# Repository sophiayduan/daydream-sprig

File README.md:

# Daydream-Sprig

#### The Daydream-Sprig is a version of the [Sprig](https://github.com/hackclub/sprig) using the bare RP2040 chip and in a vertical handheld formfactor.

I'll be setting it up the same as the Sprig. flashing Spade OS (Sprigs custom operating system)

### Features 
- All pre-exsiting sprig stuff (Rp2040, ST7735 1.8" Display, powered via 2xaaa, etc)
- 6x6mm push buttons
- Vertical handheld form factor
- 4 additional GPIOS
- Cool silkscreen art made by Erin + some stolen from the og sprig

(unlike the original sprig, this board doesn't include a speaker due to its cost)

This project was made as a lanyard for [Daydream Ottawa](https://daydream.hackclub.com/ottawa) organizers (to display their names and other cool stuff) but, I didn't end up finishing it in time oops.

## Acknowledgements
*the sprig.*

Thanks JLCPCB for sponsoring DD Ottawa and hence this project.

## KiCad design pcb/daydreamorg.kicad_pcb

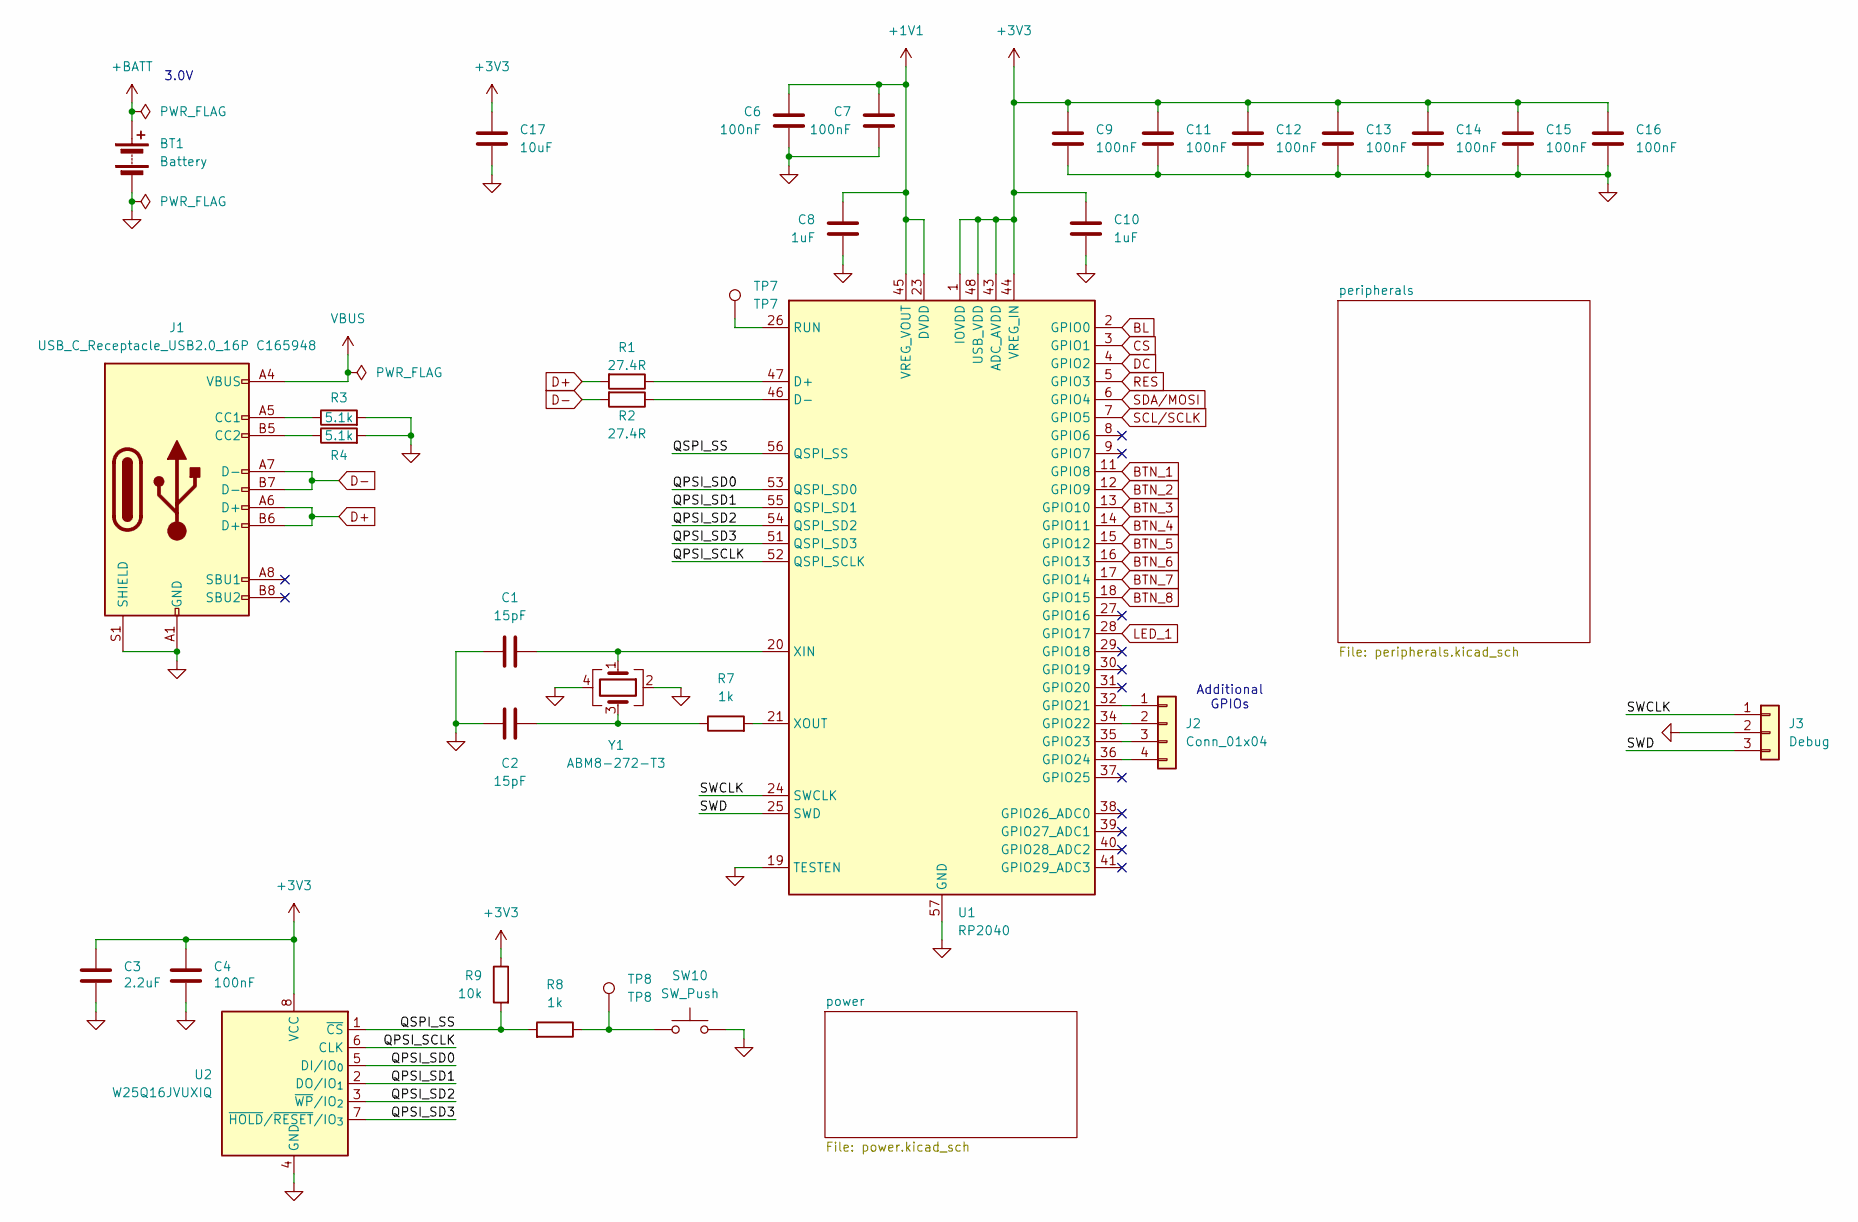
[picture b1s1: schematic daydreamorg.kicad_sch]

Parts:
BT1: Battery; BatteryHolder_Keystone_2468_2xAAA; LCSC C254917
C1, C2: 15pF; C_0402_1005Metric; LCSC C1548
C3: 2.2uF; C_0402_1005Metric; LCSC C541409
C4: 100nF; C_0603_1608Metric; LCSC C1525
C6, C7, C9, C11, C12, C13, C14, C15, C16: 100nF; C_0402_1005Metric; LCSC C1525
C8, C10: 1uF; C_0402_1005Metric; LCSC C52923
C17: 10uF; C_0805_2012Metric
J1: USB_C_Receptacle_USB2.0_16P C165948; USB_C_Receptacle_HRO_TYPE-C-31-M-12; LCSC C165948
J2: Conn_01x04; PinHeader_1x04_P2.54mm_Vertical
J3: Debug; PinHeader_1x03_P2.54mm_Vertical
R1, R2: 27.4R; R_0402_1005Metric; LCSC C25100
R3, R4: 5.1k; R_0603_1608Metric; LCSC C23186
R7, R8: 1k; R_0402_1005Metric; LCSC C11702
R9: 10k; R_0402_1005Metric
SW10: SW_Push; SW_TS-1088-AR02016; LCSC C720477
TP7: TP7; TestPoint_Pad_D2.0mm
TP8: TP8; TestPoint_Pad_D2.0mm
U1: RP2040; QFN-56-1EP_7x7mm_P0.4mm_EP3.2x3.2mm; LCSC C2040
U2: W25Q16JVUXIQ; SOIC-8_5.3x5.3mm_P1.27mm; LCSC C2843335
Y1: ABM8-272-T3; Crystal_SMD_3225-4Pin_3.2x2.5mm; LCSC C20625731

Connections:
+1V1: C6.1, C7.1, C8.1, U1.23 (DVDD), U1.45 (VREG_VOUT), U1.50 (DVDD)
+3V3: C3.1, C4.1, C9.1, C10.1, C11.1, C12.1, C13.1, C14.1, C15.1, C16.1, C17.1, R9.1, U1.1 (IOVDD), U1.10 (IOVDD), U1.22 (IOVDD), U1.33 (IOVDD), U1.42 (IOVDD), U1.43 (ADC_AVDD), U1.44 (VREG_IN), U1.48 (USB_VDD), U1.49 (IOVDD), U2.8 (VCC); also elsewhere on the board
+BATT: BT1.1 (+); also elsewhere on the board
/QPSI_SCLK: U1.52 (QSPI_SCLK), U2.6 (CLK)
/QPSI_SD0: U1.53 (QSPI_SD0), U2.5 (DI/IO_{0})
/QPSI_SD1: U1.55 (QSPI_SD1), U2.2 (DO/IO_{1})
/QPSI_SD2: U1.54 (QSPI_SD2), U2.3 (~WP/IO_{2})
/QPSI_SD3: U1.51 (QSPI_SD3), U2.7 (~HOLD/~RESET/IO_{3})
/QSPI_SS: R8.2, R9.2, U1.56 (QSPI_SS), U2.1 (~CS)
/SWCLK: J3.1, U1.24 (SWCLK)
/SWD: J3.3, U1.25 (SWD)
BL: U1.2 (GPIO0); also elsewhere on the board
BTN_1: U1.11 (GPIO8); also elsewhere on the board
BTN_2: U1.12 (GPIO9); also elsewhere on the board
BTN_3: U1.13 (GPIO10); also elsewhere on the board
BTN_4: U1.14 (GPIO11); also elsewhere on the board
BTN_5: U1.15 (GPIO12); also elsewhere on the board
BTN_6: U1.16 (GPIO13); also elsewhere on the board
BTN_7: U1.17 (GPIO14); also elsewhere on the board
BTN_8: U1.18 (GPIO15); also elsewhere on the board
CS: U1.3 (GPIO1); also elsewhere on the board
D+: J1.A6 (D+), J1.B6 (D+), R1.2
D-: J1.A7 (D-), J1.B7 (D-), R2.2
DC: U1.4 (GPIO2); also elsewhere on the board
GND: BT1.2 (-), C1.1, C2.1, C3.2, C4.2, C6.2, C7.2, C8.2, C9.2, C10.2, C11.2, C12.2, C13.2, C14.2, C15.2, C16.2, C17.2, J1.A1 (GND), J1.A12 (GND), J1.B1 (GND), J1.B12 (GND), J1.S1 (SHIELD), J3.2, R3.2, R4.2, SW10.2, U1.19 (TESTEN), U1.57 (GND), U2.4 (GND), Y1.2, Y1.4; also elsewhere on the board
LED_1: U1.28 (GPIO17); also elsewhere on the board
unnamed: C2.2, R7.1, Y1.3
unnamed: J1.A5 (CC1), R3.1
unnamed: J1.B5 (CC2), R4.1
unnamed: J2.1, U1.32 (GPIO21)
unnamed: J2.2, U1.34 (GPIO22)
unnamed: J2.3, U1.35 (GPIO23)
unnamed: J2.4, U1.36 (GPIO24)
unnamed: R8.1, SW10.1, TP8.1
unnamed: R1.1, U1.47 (D+)
unnamed: R2.1, U1.46 (D-)
unnamed: TP7.1, U1.26 (RUN)
unnamed: C1.2, U1.20 (XIN), Y1.1
unnamed: R7.2, U1.21 (XOUT)
RES: U1.5 (GPIO3); also elsewhere on the board
SCL/SCLK: U1.7 (GPIO5); also elsewhere on the board
SDA/MOSI: U1.6 (GPIO4); also elsewhere on the board
VBUS: J1.A4 (VBUS), J1.A9 (VBUS), J1.B4 (VBUS), J1.B9 (VBUS); also elsewhere on the board

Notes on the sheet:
Additional GPIOs
3.0V

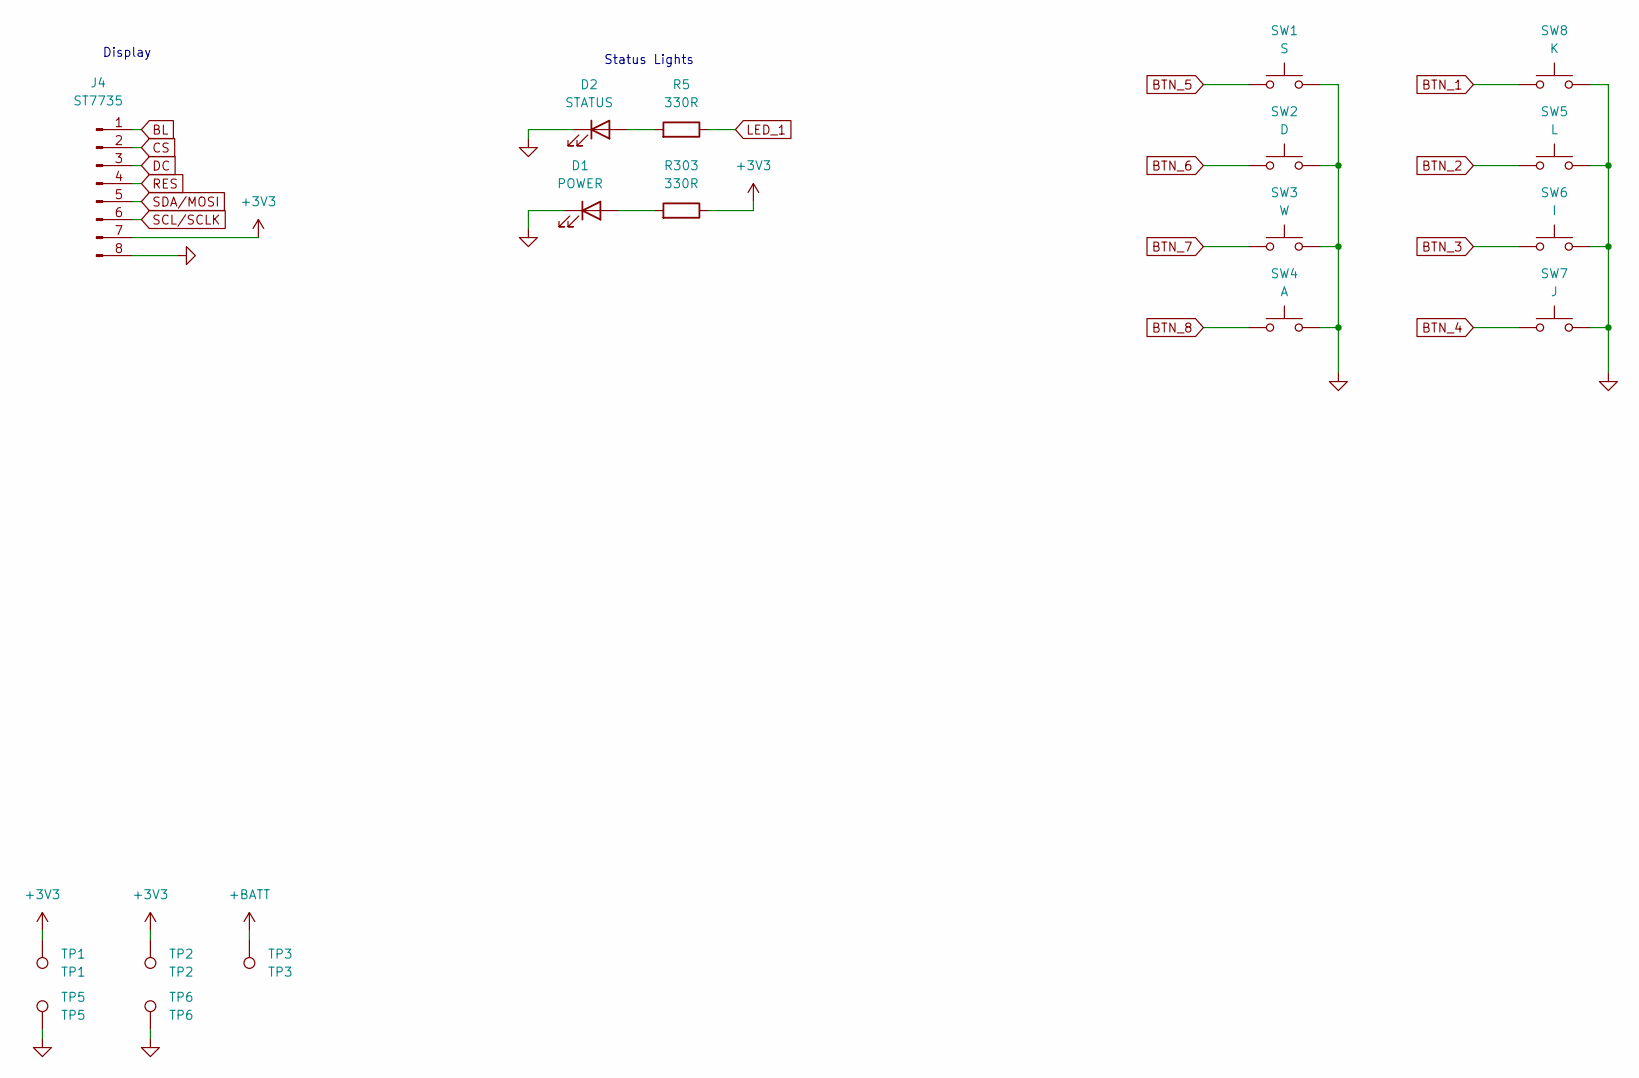
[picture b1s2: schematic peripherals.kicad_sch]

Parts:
D1: POWER; LED_1206_3216Metric_Pad1.42x1.75mm_HandSolder; LCSC C14641
D2: STATUS; LED_1206_3216Metric_Pad1.42x1.75mm_HandSolder; LCSC C49018
J4: ST7735; st7735
R5, R303: 330R; R_0402_1005Metric; LCSC C25104
SW1: S; SW_PUSH_6mm; LCSC C83205
SW2: D; SW_PUSH_6mm; LCSC C83205
SW3: W; SW_PUSH_6mm; LCSC C83205
SW4: A; SW_PUSH_6mm; LCSC C83205
SW5: L; SW_PUSH_6mm; LCSC C83205
SW6: I; SW_PUSH_6mm; LCSC C83205
SW7: J; SW_PUSH_6mm; LCSC C83205
SW8: K; SW_PUSH_6mm; LCSC C83205
TP1: TP1; TestPoint_Pad_D2.0mm
TP2: TP2; TestPoint_Pad_D2.0mm
TP3: TP3; TestPoint_Pad_D2.0mm
TP5: TP5; TestPoint_Pad_D2.0mm
TP6: TP6; TestPoint_Pad_D2.0mm

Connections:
+3V3: J4.7, R303.1, TP1.1, TP2.1; also elsewhere on the board
+BATT: TP3.1; also elsewhere on the board
BL: J4.1; also elsewhere on the board
BTN_1: SW8.1; also elsewhere on the board
BTN_2: SW5.1; also elsewhere on the board
BTN_3: SW6.1; also elsewhere on the board
BTN_4: SW7.1; also elsewhere on the board
BTN_5: SW1.1; also elsewhere on the board
BTN_6: SW2.1; also elsewhere on the board
BTN_7: SW3.1; also elsewhere on the board
BTN_8: SW4.1; also elsewhere on the board
CS: J4.2; also elsewhere on the board
DC: J4.3; also elsewhere on the board
GND: D1.1 (K), D2.1 (K), J4.8, SW1.2, SW2.2, SW3.2, SW4.2, SW5.2, SW6.2, SW7.2, SW8.2, TP5.1, TP6.1; also elsewhere on the board
LED_1: R5.1; also elsewhere on the board
unnamed: D1.2 (A), R303.2
unnamed: D2.2 (A), R5.2
RES: J4.4; also elsewhere on the board
SCL/SCLK: J4.6; also elsewhere on the board
SDA/MOSI: J4.5; also elsewhere on the board

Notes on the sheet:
Display
Status Lights

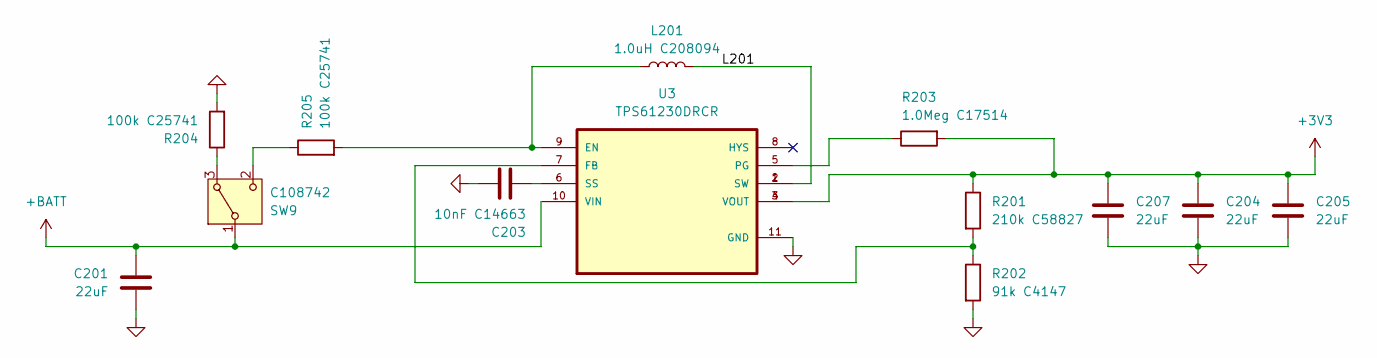
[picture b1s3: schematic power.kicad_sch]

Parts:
C201: 22uF; C_0805_2012Metric; LCSC C77071
C203: 10nF C14663; C_0603_1608Metric; LCSC C14663
C204, C205, C207: 22uF; C_0805_2012Metric; LCSC C92811
L201: 1.0uH C208094; Untitled_1; LCSC C208094
R201: 210k C58827; R_0402_1005Metric; LCSC C58827
R202: 91k C4147; R_0402_1005Metric; LCSC C4147
R203: 1.0Meg C17514; R_0805_2012Metric; LCSC C17514
R204, R205: 100k C25741; R_0402_1005Metric; LCSC C25741
SW9: C108742; slide switch; LCSC C108742
U3: TPS61230DRCR; TPS123

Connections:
+3V3: C204.1, C205.1, C207.1, R201.1, R203.2, U3.3 (VOUT), U3.4 (VOUT); also elsewhere on the board
+BATT: C201.1, SW9.1 (B), U3.10 (VIN); also elsewhere on the board
/power/L201: L201.2, U3.1 (SW), U3.2 (SW)
GND: C201.2, C203.2, C204.2, C205.2, C207.2, R202.2, R204.2, U3.11 (GND); also elsewhere on the board
unnamed: R204.1, SW9.3 (A)
unnamed: R205.1, SW9.2 (C)
unnamed: L201.1, R205.2, U3.9 (EN)
unnamed: R201.2, R202.1, U3.7 (FB)
unnamed: R203.1, U3.5 (PG)
unnamed: C203.1, U3.6 (SS)

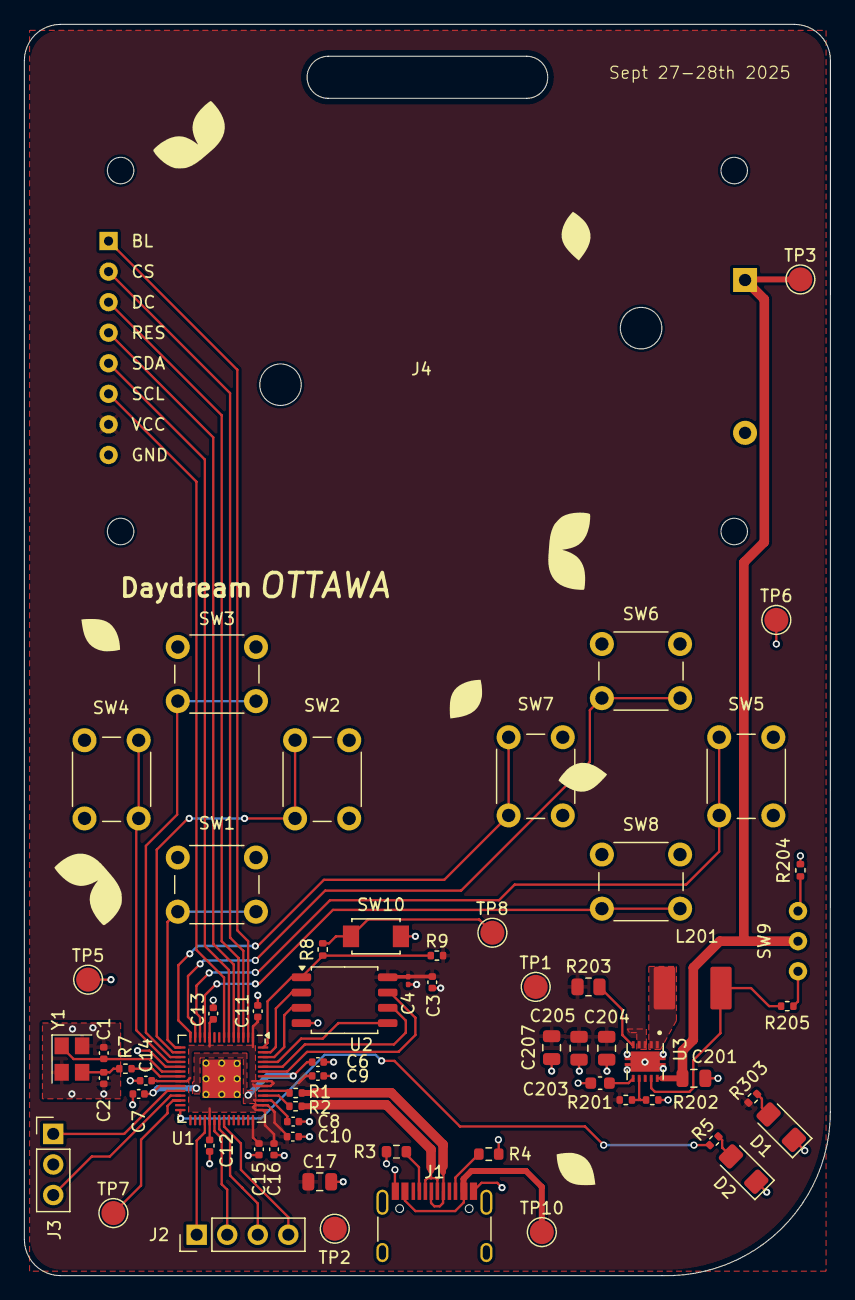
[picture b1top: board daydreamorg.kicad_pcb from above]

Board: 2 copper layers, 67.0 x 104.0 mm, 65 parts (1 on the bottom side), 52 nets.

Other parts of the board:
TP10: TestPoint; TestPoint_Pad_D2.0mm

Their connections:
VBUS: TP10.1; also elsewhere on the board

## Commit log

2025-09-18 add to readme
2025-10-25 add jlcpcb and clean up some text
    Updated project description and features list.
2025-10-27 add final conclusion + time
2025-10-27 update total time
2025-10-27 move pcb files into folder
2025-10-27 add pcb images
